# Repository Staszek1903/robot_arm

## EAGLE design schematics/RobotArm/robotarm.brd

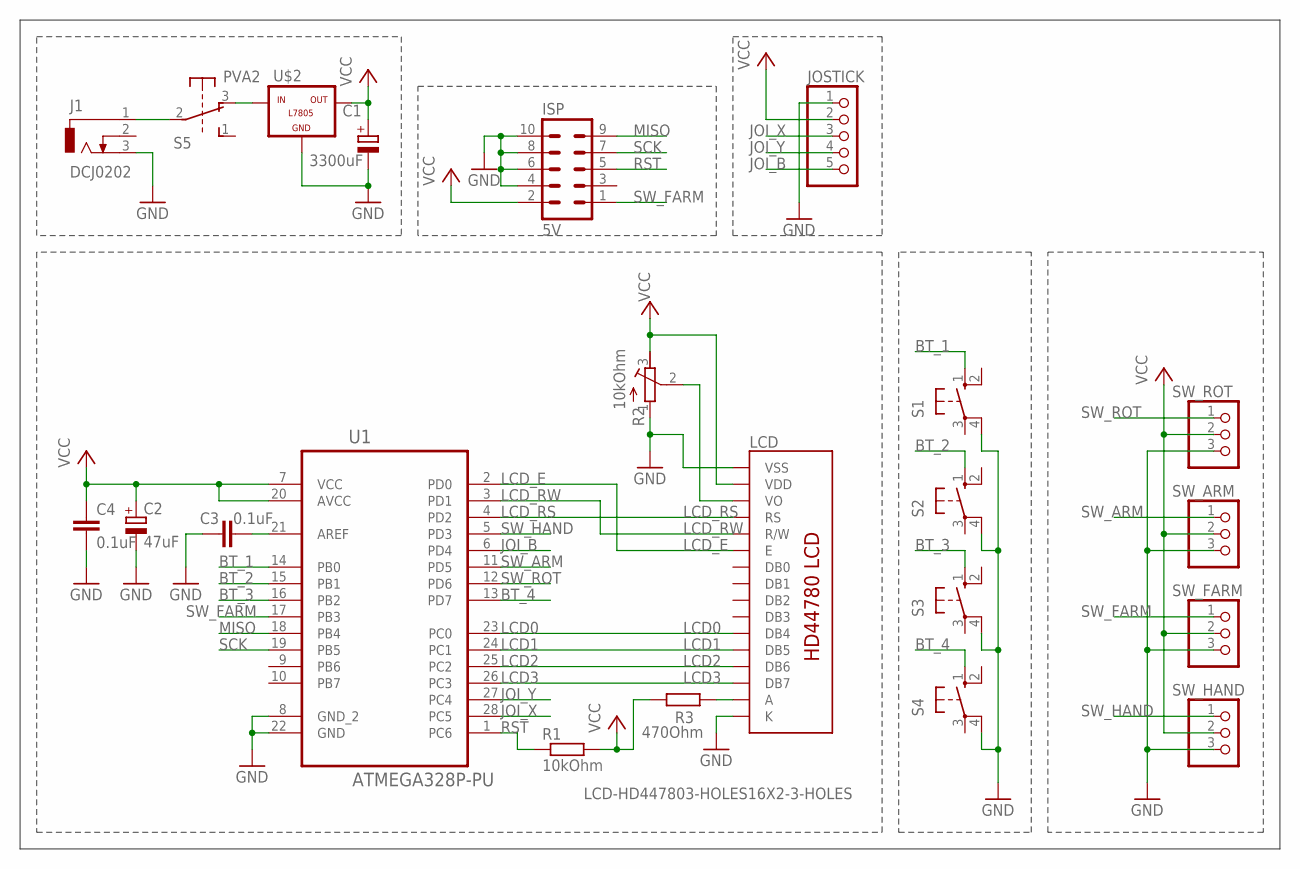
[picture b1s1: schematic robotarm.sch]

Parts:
C1: 3300uF; E3,5-10
C2: 47uF; E2,5-6
C3, C4: 0.1uF; C025-024X044
ISP: 5V; ML10
J1: DCJ0202
JOSTICK: PINHD-1X5; 1X05
LCD: LCD-HD447803-HOLES16X2-3-HOLES; LCD-16X2-3HOLES
R1: 10kOhm; 0204/7
R2: 10kOhm; RTRIM3339P
R3: 470Ohm; 0204/7
S1, S2, S3, S4: 10-XX; B3F-10XX
S5: PVA2; PVA2F
SW_ARM: PINHD-1X3; 1X03
SW_FARM: PINHD-1X3; 1X03
SW_HAND: PINHD-1X3; 1X03
SW_ROT: PINHD-1X3; 1X03
U1: ATMEGA328P-PU; DIP254P762X457-28
U$2: -L7805; L7805

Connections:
BT_1: S1.1 (S), U1.14 (PB0)
BT_2: S2.1 (S), U1.15 (PB1)
BT_3: S3.1 (S), U1.16 (PB2)
BT_4: S4.1 (S), U1.13 (PD7)
GND: C1.-, C2.-, C3.1, C4.2, ISP.4, ISP.6, ISP.8, ISP.10, J1.3, JOSTICK.1, LCD.1 (VSS), LCD.16 (K), R2.1 (A), S1.4 (P1), S2.4 (P1), S3.4 (P1), S4.4 (P1), SW_ARM.3, SW_FARM.3, SW_HAND.3, SW_ROT.3, U1.8 (GND_2), U1.22 (GND), U$2.GND
JOI_B: JOSTICK.5, U1.6 (PD4)
JOI_X: JOSTICK.3, U1.28 (PC5)
JOI_Y: JOSTICK.4, U1.27 (PC4)
LCD0: LCD.11 (DB4), U1.23 (PC0)
LCD1: LCD.12 (DB5), U1.24 (PC1)
LCD2: LCD.13 (DB6), U1.25 (PC2)
LCD3: LCD.14 (DB7), U1.26 (PC3)
LCD_E: LCD.6 (E), U1.2 (PD0)
LCD_RS: LCD.4 (RS), U1.4 (PD2)
LCD_RW: LCD.5 (R/W), U1.3 (PD1)
MISO: ISP.9, U1.18 (PB4)
unnamed: J1.1, S5.2
unnamed: S5.3 (O), U$2.IN
unnamed: LCD.3 (VO), R2.2 (S)
unnamed: LCD.15 (A), R3.2
unnamed: C3.2, U1.21 (AREF)
RST: ISP.5, R1.1, U1.1 (PC6)
SCK: ISP.7, U1.19 (PB5)
SW_ARM: SW_ARM.1, U1.11 (PD5)
SW_FARM: ISP.1, SW_FARM.1, U1.17 (PB3)
SW_HAND: SW_HAND.1, U1.5 (PD3)
SW_ROT: SW_ROT.1, U1.12 (PD6)
VCC: C1.+, C2.+, C4.1, ISP.2, JOSTICK.2, LCD.2 (VDD), R1.2, R2.3 (E), R3.1, SW_ARM.2, SW_FARM.2, SW_HAND.2, SW_ROT.2, U1.7 (VCC), U1.20 (AVCC), U$2.OUT

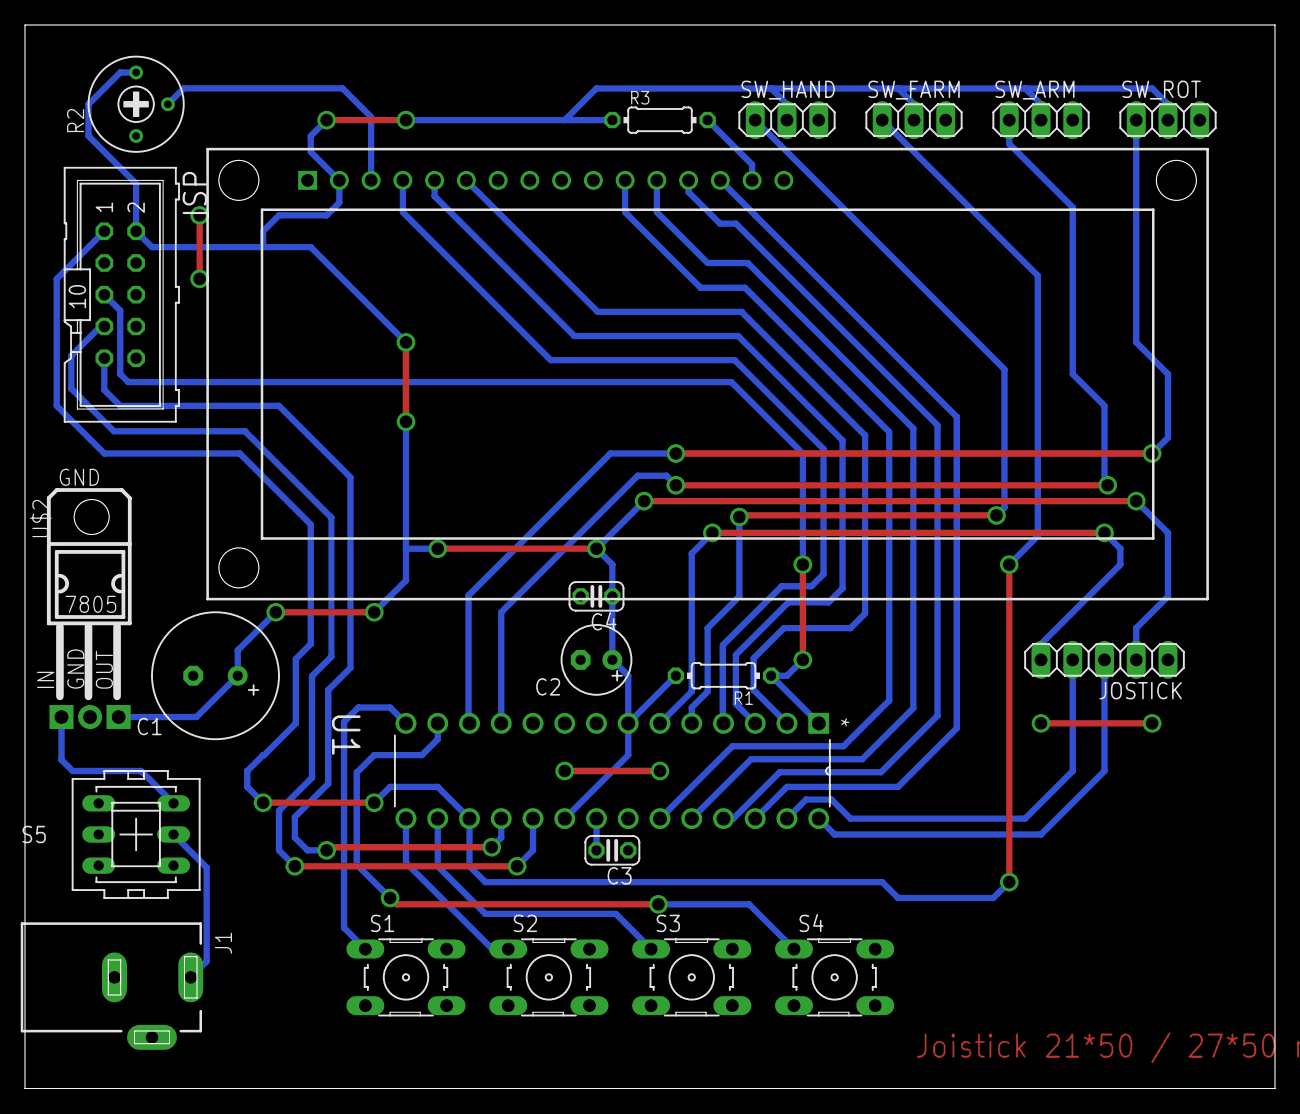
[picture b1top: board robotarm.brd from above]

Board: 2 copper layers, 100.0 x 85.1 mm, 22 parts (0 on the bottom side), 28 nets.

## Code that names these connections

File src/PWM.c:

#include "../inc/PWM.h"

void PWM0_init()
{
	DDRD |= (1<<6) | (1<<5);
	PORTD &= ~((1<<6) | (1<<5));	// USTAWIENIA DLA OC0B i OC0A (PD5, PD6)
	
 	TCCR0A = (1<<COM0A1) |  (1<<COM0B1) | ( 1<<WGM00) | (1<<WGM01); 
 	//FAST PWM, clear on compare, set at top A&B
 	
 	OCR0A = 0; //init PWMs
 	OCR0B = 0;
 	
 	TCCR0B =  (1<<CS00) | /*| (1<<CS01) ;| (1<<WGM02); */ (1<<CS02); 
 	// start time Prescaler = 256;
}

void PWM2_init()
{
	
	DDRD |= (1<<3);
	PORTD &= ~(1<<3);
	DDRB |= (1<<3);
	PORTB &= ~(1<<3);	// USTAWIENIA DLA OC2B i OC2A (PD3, PB3)
	
 	TCCR2A = (1<<COM2A1) |  (1<<COM2B1) | ( 1<<WGM20) | (1<<WGM21);
 	//FAST PWM, clear on compare, set at top A&B
 	
 	OCR2A = 0; //init PWMs
 	OCR2B = 0;
 	
 	TCCR2B =  (1<<CS20) |  (1<<CS21) | (1<<CS22); 
 	// start time Prescaler = 256;
}

void PWM_setval0A(uint8_t val)
{
	OCR0A = val;
}

void PWM_setval0B(uint8_t val)
{
	OCR0B = val;
}

void PWM_setval2A(uint8_t val)
{
	OCR2A = val;
}
void PWM_setval2B(uint8_t val)
{
	OCR2B = val;
}

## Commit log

2019-03-21 schematics
